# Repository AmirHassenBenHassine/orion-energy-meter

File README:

# Orion Energy Monitor

A three-phase energy monitoring system built on ESP32 for real-time power consumption tracking and reporting.

## Overview

The Orion Energy Monitor measures voltage and current across three phases, calculates power consumption, and transmits data via MQTT. It supports WiFi provisioning through a captive portal, OTA firmware updates, and battery-powered operation with light sleep for power efficiency.

## Hardware Requirements

- ESP32 development board
- ZMPT101B voltage sensor module
- 3x SCT-013 current transformer sensors 
- Li-ion battery with charging circuit 
- Status LEDs (power, WiFi, charging, battery)
- Push buttons for WiFi pairing and hard reset

## Pin Configuration

| Function | GPIO |
|----------|------|
| Voltage Sensor | 32 |
| Current Phase R | 39 |
| Current Phase Y | 34 |
| Current Phase B | 35 |
| Battery Voltage | 36 |
| Power LED | 14 |
| WiFi LED | 27 |
| Charging LED | 26 |
| Battery LED | 25 |
| WiFi Pairing Button | 4 |
| Hard Reset Button | 13 |
| Charging Status | 33 |

## Features

### Energy Monitoring
- Three-phase voltage and current measurement
- Real-time power calculation per phase
- Cumulative energy tracking (kWh)
- Configurable calibration values

### Connectivity
- WiFi with captive portal for initial setup
- MQTT for data transmission
- mDNS service discovery for broker detection
- Automatic reconnection handling

### Power Management
- Light sleep between measurement cycles
- Battery voltage monitoring
- Charging status detection
- LED indicators for system status

### Firmware Updates
- OTA updates from GitHub releases
- ETag-based update detection
- Rollback protection

## Building

### Prerequisites

- PlatformIO CLI or IDE
- ESP32 board support

### Build Commands

```bash
# Build firmware
pio run -e esp32dev

# Upload to device
pio run -t upload -e esp32dev

# Monitor serial output
pio device monitor
```

## Configuration

Edit `include/config.h` to modify:

- `DATA_SEND_INTERVAL_MS` - Interval between measurements (default: 30000ms)
- `MQTT_BROKER_HOST` - MQTT broker hostname
- `MQTT_BROKER_PORT` - MQTT broker port (default: 1883)
- `VOLTAGE_CALIBRATION` - Voltage sensor calibration factor
- `CURRENT_CALIBRATION_DEFAULT` - Current sensor calibration factor

## MQTT Topics

| Topic | Direction | Description |
|-------|-----------|-------------|
| `energy/metrics` | Publish | JSON payload with energy data |
| `orion/status` | Publish | Device connection status |
| `orion/config` | Subscribe | WiFi credential updates |
| `orion/trigger` | Subscribe | Remote commands |
| `orion/refresh` | Subscribe | Network scan requests |

### Metrics Payload Format

```json
{
  "deviceId": "XXXXXXXXXXXX",
  "battery": 85.5,
  "timestamp": "2025-01-15 14:30:00",
  "voltage": 230.5,
  "totalPower": 1500.0,
  "energyTotal": 12.5,
  "phases": [
    {"current": 2.1, "power": 483.0},
    {"current": 2.3, "power": 529.0},
    {"current": 2.1, "power": 488.0}
  ]
}
```

## WiFi Provisioning

1. Hold the WiFi pairing button during boot
2. Connect to the "OrionSetup" access point
3. Configure WiFi credentials through the captive portal
4. Device will restart and connect to the configured network

## Hard Reset

Hold the hard reset button during boot to erase all stored credentials and settings. The device will restart in provisioning mode.

## MQTT Broker Setup

The device uses mDNS to discover MQTT brokers. For automatic discovery, configure your broker to advertise via mDNS:

### Mosquitto on Linux

Create `/etc/avahi/services/mosquitto.service`:

```xml
<?xml version="1.0" standalone='no'?>
<!DOCTYPE service-group SYSTEM "avahi-service.dtd">
<service-group>
  <name>Mosquitto MQTT Broker</name>
  <service>
    <type>_mqtt._tcp</type>
    <port>1883</port>
  </service>
</service-group>
```

Restart Avahi:

```bash
sudo systemctl restart avahi-daemon
```

## Calibration

### Voltage Calibration

1. Measure actual mains voltage with a multimeter
2. Compare with reported voltage
3. Adjust `VOLTAGE_CALIBRATION` in config.h:
   ```
   new_cal = current_cal * (actual_voltage / reported_voltage)
   ```

### Current Calibration

1. Connect a known load
2. Measure actual current with a clamp meter
3. Adjust `CURRENT_CALIBRATION_DEFAULT` similarly

## Project Structure

```
orion_monitor/
├── include/
│   ├── config.h           # Configuration constants
│   ├── battery_manager.h
│   ├── ble_manager.h
│   ├── button_manager.h
│   ├── energy_sensor.h
│   ├── led_manager.h
│   ├── mqtt_manager.h
│   ├── ota_manager.h
│   ├── utils.h
│   └── wifi_manager.h
├── src/
│   ├── main.cpp           # Application entry point
│   ├── battery_manager.cpp
│   ├── ble_manager.cpp
│   ├── button_manager.cpp
│   ├── energy_sensor.cpp
│   ├── led_manager.cpp
│   ├── mqtt_manager.cpp
│   ├── ota_manager.cpp
│   ├── utils.cpp
│   └── wifi_manager.cpp
├── platformio.ini         # Build configuration
└── README.md
```

## Dependencies

Managed automatically by PlatformIO:

- WiFiManager
- PubSubClient
- ArduinoJson
- EmonLib
- NimBLE-Arduino

## Troubleshooting

### Device not connecting to WiFi
- Verify credentials are correct
- Check signal strength
- Try moving closer to the access point
- Use hard reset to clear stored credentials

### MQTT connection failing
- Verify broker is running and accessible
- Check firewall settings
- Ensure mDNS/Avahi is configured on broker host
- Check broker logs for connection attempts

### Incorrect readings
- Verify sensor connections
- Check calibration values
- Ensure CT sensors are oriented correctly on the wire
- Confirm voltage sensor is connected to live and neutral

### High power consumption
- Reduce `DATA_SEND_INTERVAL_MS` 
- Check for floating GPIO pins

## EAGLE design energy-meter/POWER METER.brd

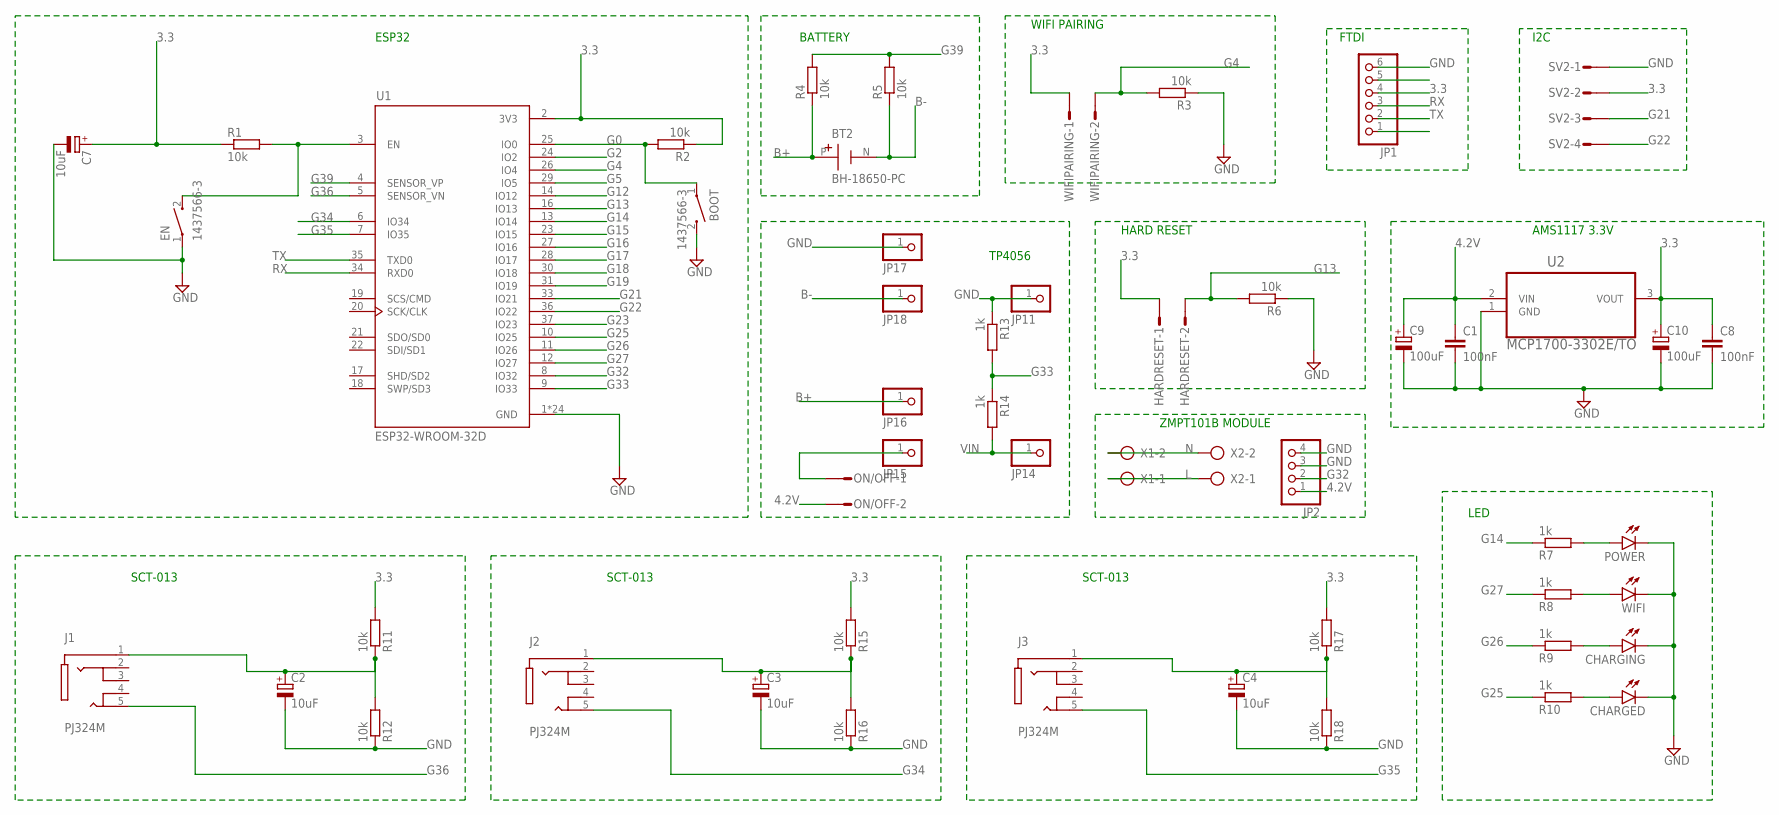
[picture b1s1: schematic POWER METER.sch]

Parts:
BOOT: 1437566-3; SW_1437566-3
BT2: BH-18650-PC; BAT_BH-18650-PC
C1, C8: 100nF; C1206K
C2, C3, C4, C7: 10uF; E2,5-6
C9, C10: 100uF; E2,5-6
CHARGED: LEDCHIPLED_1206; CHIPLED_1206
CHARGING: LEDCHIPLED_1206; CHIPLED_1206
EN: 1437566-3; SW_1437566-3
HARDRESET: S02P
J1, J2, J3: PJ324M; WENZHOU_PJ324M
JP1: PINHD-1X6/90; 1X06/90
JP2: PINHD-1X4; 1X04
JP11, JP14, JP15, JP16, JP17, JP18: PINHD-1X1; 1X01
ON/OFF: S02P
POWER: LEDCHIPLED_1206; CHIPLED_1206
R1, R2, R3, R4, R5, R6, R11, R12, R15, R16, R17, R18: 10k; R1206
R7, R8, R9, R10, R13, R14: 1k; R1206
SV2: S04P
U1: ESP32-WROOM-32D; MODULE_ESP32-WROOM-32D
U2: MCP1700-3302E/TO; TO127P254X495-3
WIFI: LEDCHIPLED_1206; CHIPLED_1206
WIFIPAIRING: S02P
X1, X2: AK500/2

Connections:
3.3: C7.+, C8.1, C10.+, HARDRESET.1, JP1.4, R1.1, R2.1, R11.2, R15.2, R17.2, SV2.2, U1.2 (3V3), U2.3 (VOUT), WIFIPAIRING.1
4.2V: C1.1, C9.+, JP2.1, ON/OFF.2, U2.2 (VIN)
B+: BT2.P (+), JP16.1, R4.1
B-: BT2.N (-), JP18.1, R5.1
G0: BOOT.1, R2.2, U1.25 (IO0)
G2: U1.24 (IO2)
G4: R3.2, U1.26 (IO4), WIFIPAIRING.2
G5: U1.29 (IO5)
G12: U1.14 (IO12)
G13: HARDRESET.2, R6.2, U1.16 (IO13)
G14: R7.1, U1.13 (IO14)
G15: U1.23 (IO15)
G16: U1.27 (IO16)
G17: U1.28 (IO17)
G18: U1.30 (IO18)
G19: U1.31 (IO19)
G21: SV2.3, U1.33 (IO21)
G22: SV2.4, U1.36 (IO22)
G23: U1.37 (IO23)
G25: R10.1, U1.10 (IO25)
G26: R9.1, U1.11 (IO26)
G27: R8.1, U1.12 (IO27)
G32: JP2.2, U1.8 (IO32)
G33: R13.2, R14.1, U1.9 (IO33)
G34: J2.5 (TIP_2), U1.6 (IO34)
G35: J3.5 (TIP_2), U1.7 (IO35)
G36: J1.5 (TIP_2), U1.5 (SENSOR_VN)
G39: R4.2, R5.2, U1.4 (SENSOR_VP)
GND: BOOT.2, C1.2, C2.-, C3.-, C4.-, C7.-, C8.2, C9.-, C10.-, CHARGED.C, CHARGING.C, EN.1, JP1.6, JP2.3, JP2.4, JP11.1, JP17.1, POWER.C, R3.1, R6.1, R12.1, R13.1, R16.1, R18.1, SV2.1, U1.1 (GND), U1.15 (GND), U1.38 (GND), U1.39_1 (GND), U1.39_2 (GND), U1.39_3 (GND), U1.39_4 (GND), U1.39_5 (GND), U1.39_6 (GND), U1.39_7 (GND), U1.39_8 (GND), U1.39_9 (GND), U1.39_10 (GND), U1.39_11 (GND), U1.39_12 (GND), U1.39_13 (GND), U1.39_14 (GND), U1.39_15 (GND), U1.39_16 (GND), U1.39_17 (GND), U1.39_18 (GND), U1.39_19 (GND), U1.39_20 (GND), U1.39_21 (GND), U2.1 (GND), WIFI.C
L: X1.1, X2.1
N: X1.2, X2.2
unnamed: EN.2, R1.2, U1.3 (EN)
unnamed: POWER.A, R7.2
unnamed: JP15.1, ON/OFF.1
unnamed: R8.2, WIFI.A
unnamed: CHARGING.A, R9.2
unnamed: CHARGED.A, R10.2
unnamed: C2.+, J1.1 (SLEEVE), R11.1, R12.2
unnamed: C4.+, J3.1 (SLEEVE), R17.1, R18.2
unnamed: C3.+, J2.1 (SLEEVE), R15.1, R16.2
RX: JP1.3, U1.34 (RXD0)
TX: JP1.2, U1.35 (TXD0)
VIN: JP14.1, R14.2

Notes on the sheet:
ESP32
TP4056
BATTERY
WIFI PAIRING
HARD RESET
ZMPT101B MODULE
SCT-013
LED
FTDI
I2C
AMS1117 3.3V

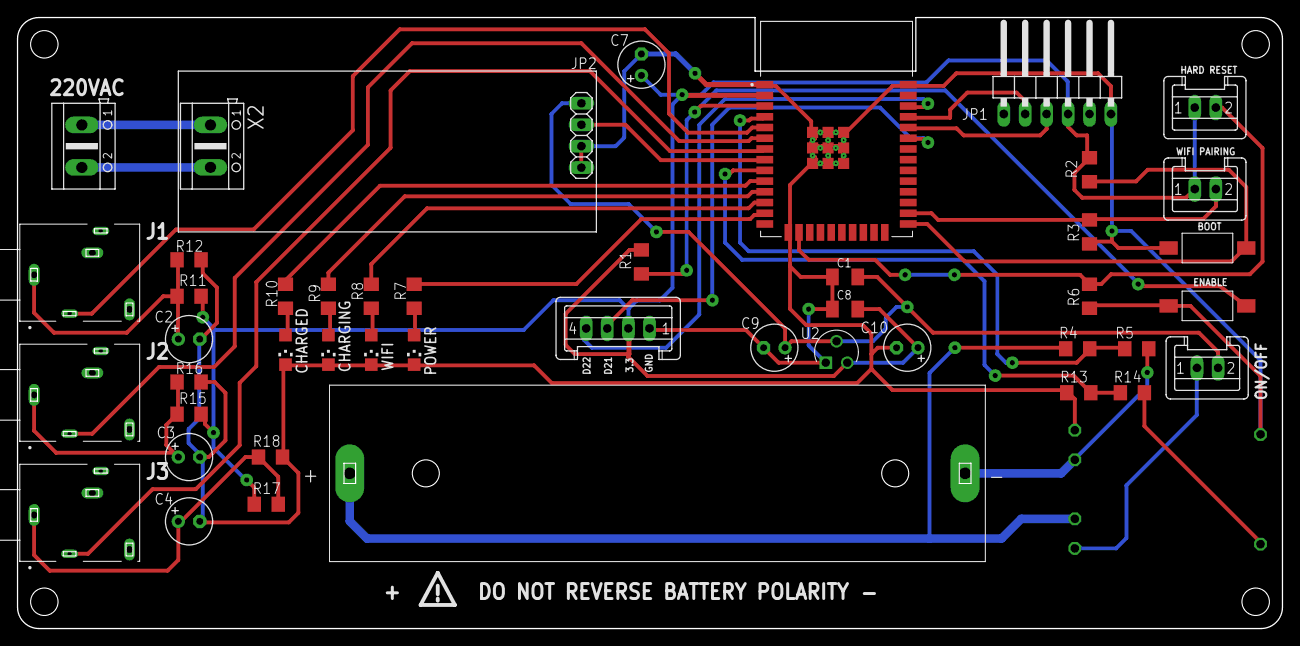
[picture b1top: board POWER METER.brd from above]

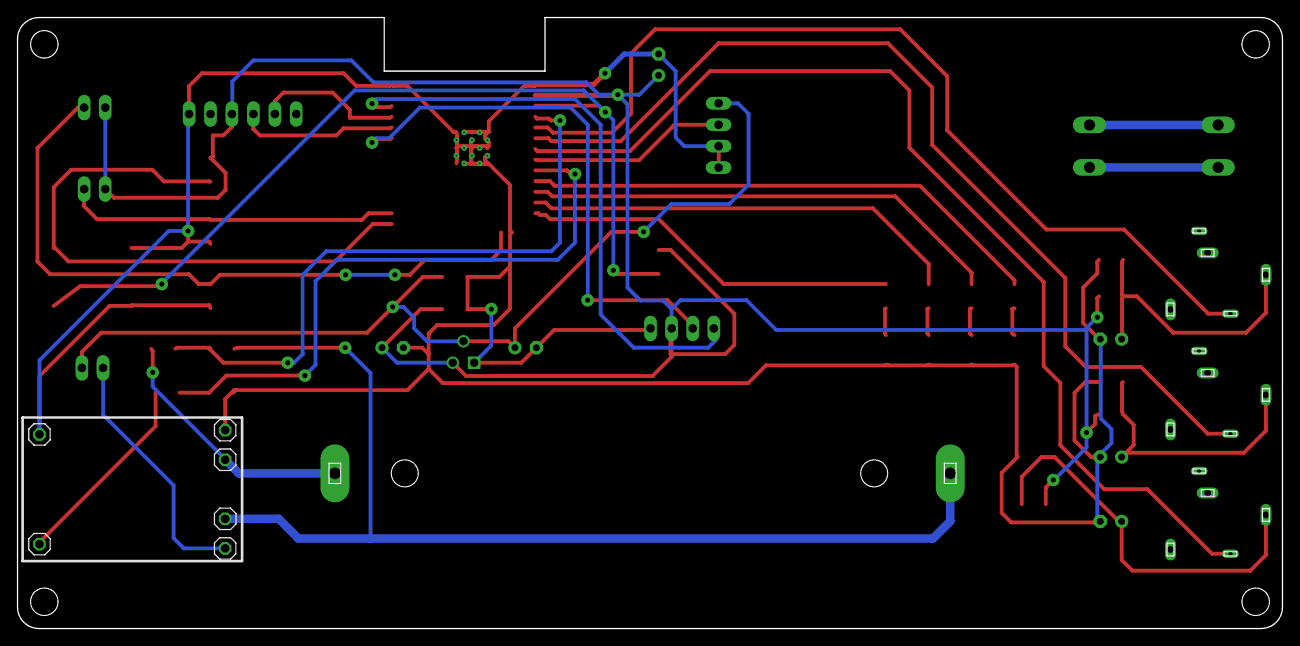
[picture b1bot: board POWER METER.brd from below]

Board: 2 copper layers, 149.9 x 72.4 mm, 52 parts (6 on the bottom side), 34 nets.

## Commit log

2025-12-07 (Add) ota manager
2025-12-08 (Update)firmware url
2025-12-08 (Fix)firmware url redirect issue
2025-12-08 (Remove) ble as its redundant
2025-12-12 fixed workflow
2025-12-16 Fixed the issues in testing and synchronised with Orion Gateway
2025-12-24 Fixed workflow and device pairing mechanism
2025-12-30 Fixed pairing workflow and finalised test scenarios
2026-01-16 Finalised tests
2026-01-19 Added OTA checksum and recovery mechanism
2026-02-06 Updated calibration and OTA URL
2026-02-06 Updated EnergyMetrics struct
2026-02-06 Added loading calibration data from NVS
2026-02-06 Fixed button logic in sleep mode
2026-04-14 Imported from private repo
2026-04-15 add CHANGELOG.md documenting v1.0.0 firmware features
2026-05-06 bump: v1.1.0 — Phase auto-detection
2026-05-06 bump: v1.2.0 — Phase auto-detection
2026-05-07 remove unecessary files
2026-05-07 add phase filter
2026-06-12 fix credentials sending bug
